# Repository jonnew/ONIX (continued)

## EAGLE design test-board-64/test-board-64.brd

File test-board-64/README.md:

# test-board-64
Test board for headstage-64. Allows injecting simulated biopotentials into
headstage modules via a selectable passive attenuator. Provides LEDs and
simulated electrical loads for optical and electrical stimulation.

## Gerber Files
{% include gerber_layers.md %}

## Bill of Materials
The BOM is located on [this google
sheet](https://docs.google.com/spreadsheets/d/1F-KWcdvH_63iXjZf0cgCfDiFX6XXW3qw6rlR8DZrFpQ/edit#gid=883728645)

## Pinout
The EIB pinout (ADC input mapping, stimulation connections, etc) is located on
[this google
sheet](https://docs.google.com/spreadsheets/d/11wRDYOqHN5lPb03yUdfXfK0zvaDYsVetplaNK-R90Gg/edit#gid=0)

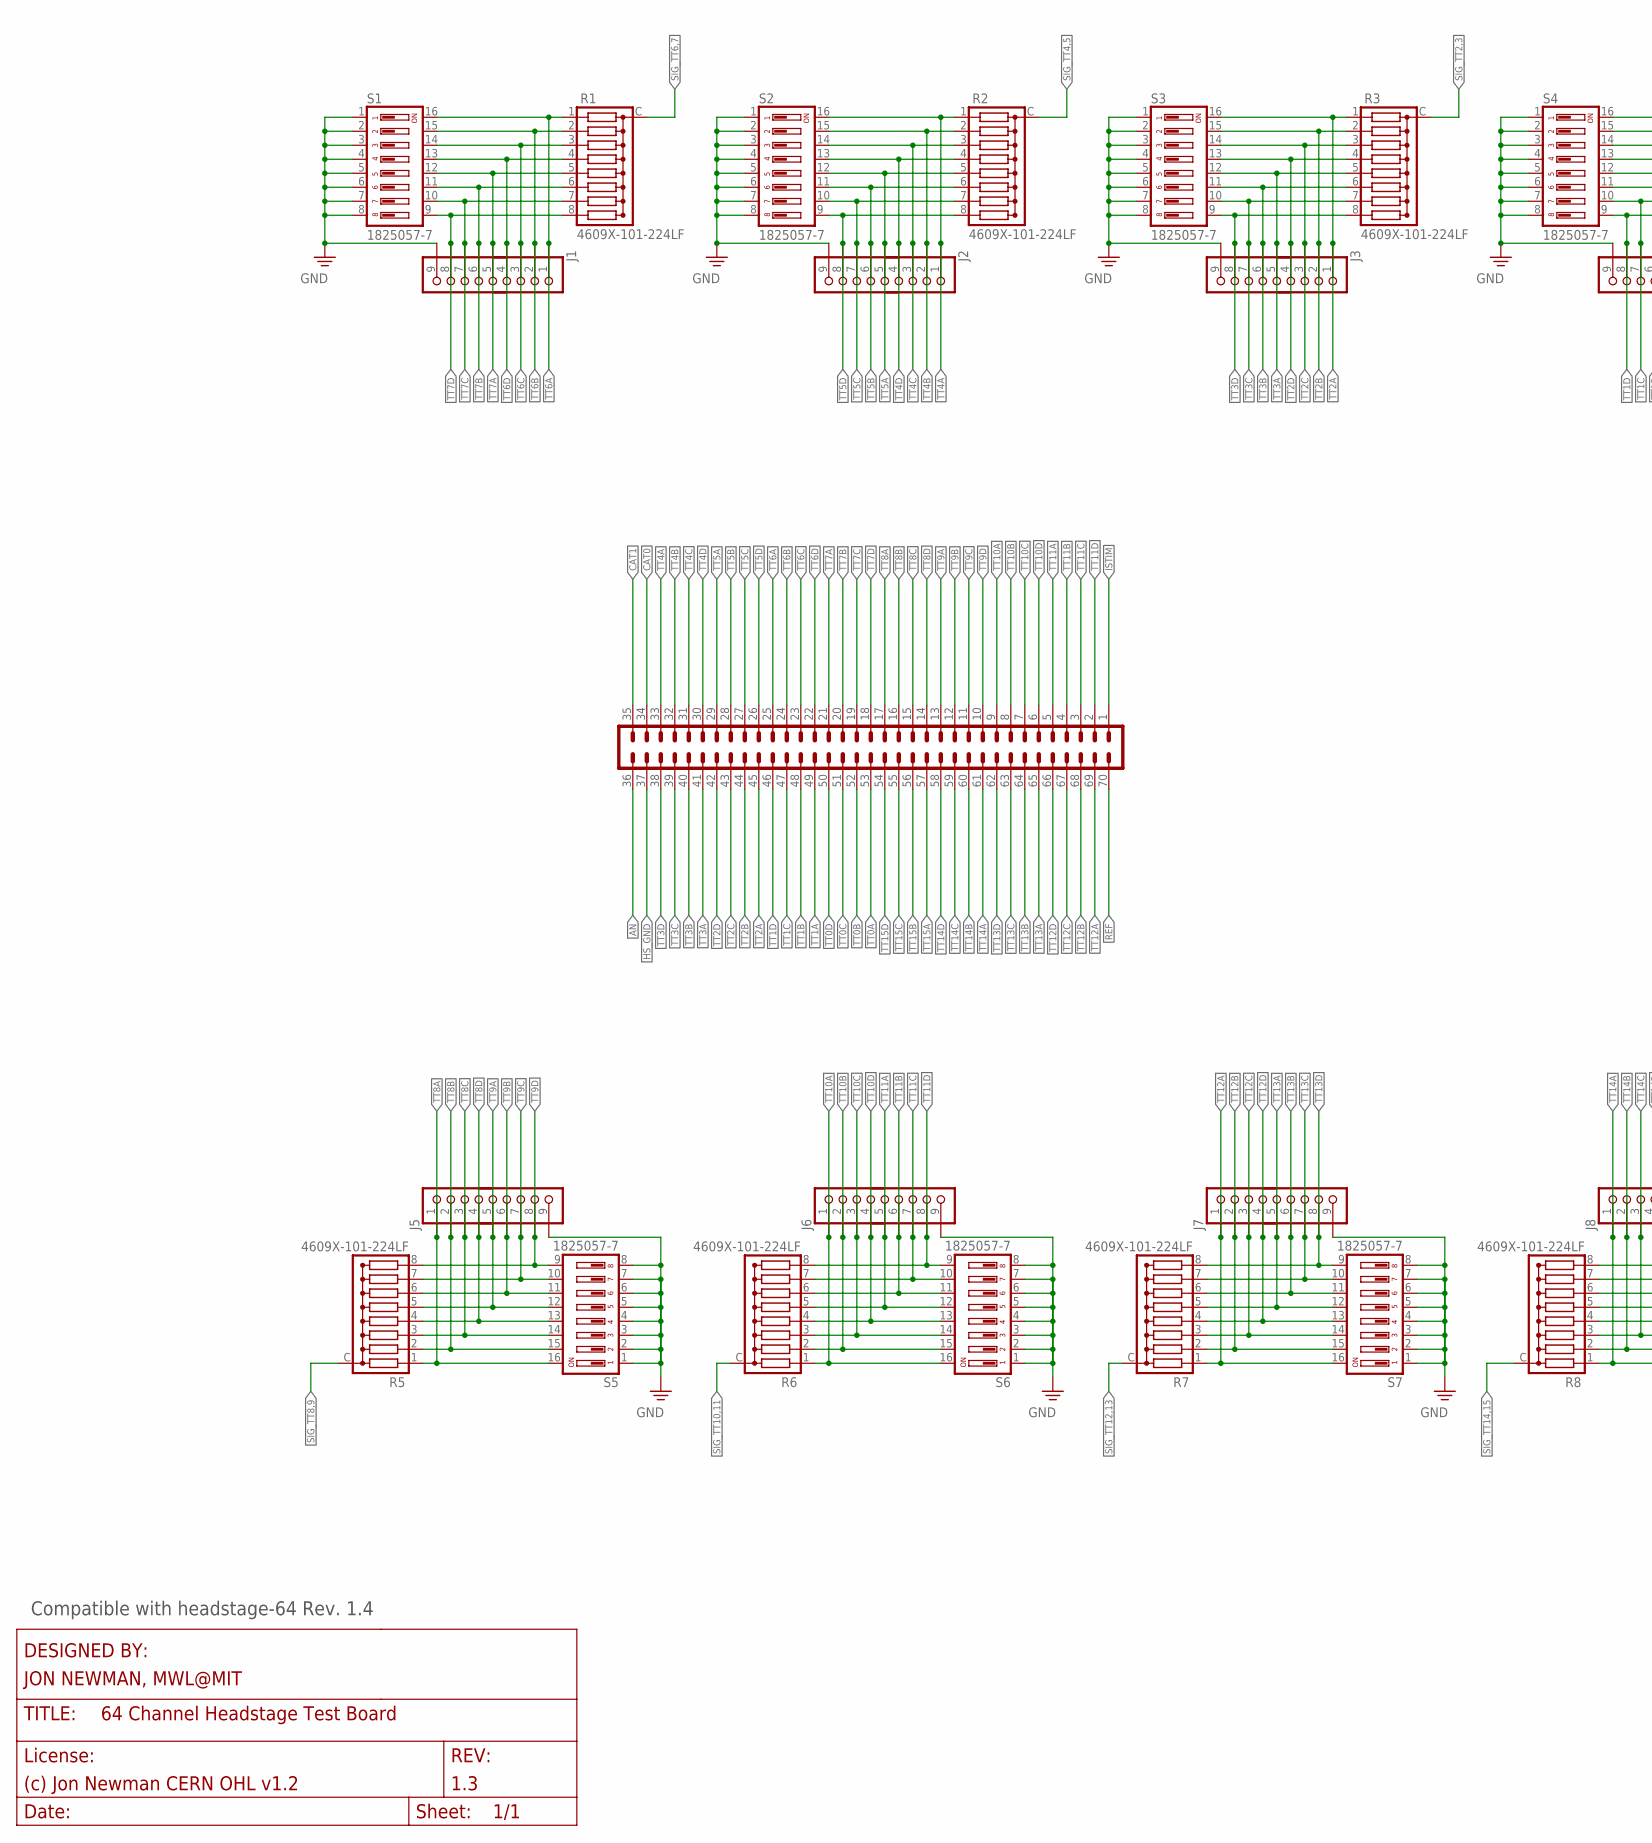
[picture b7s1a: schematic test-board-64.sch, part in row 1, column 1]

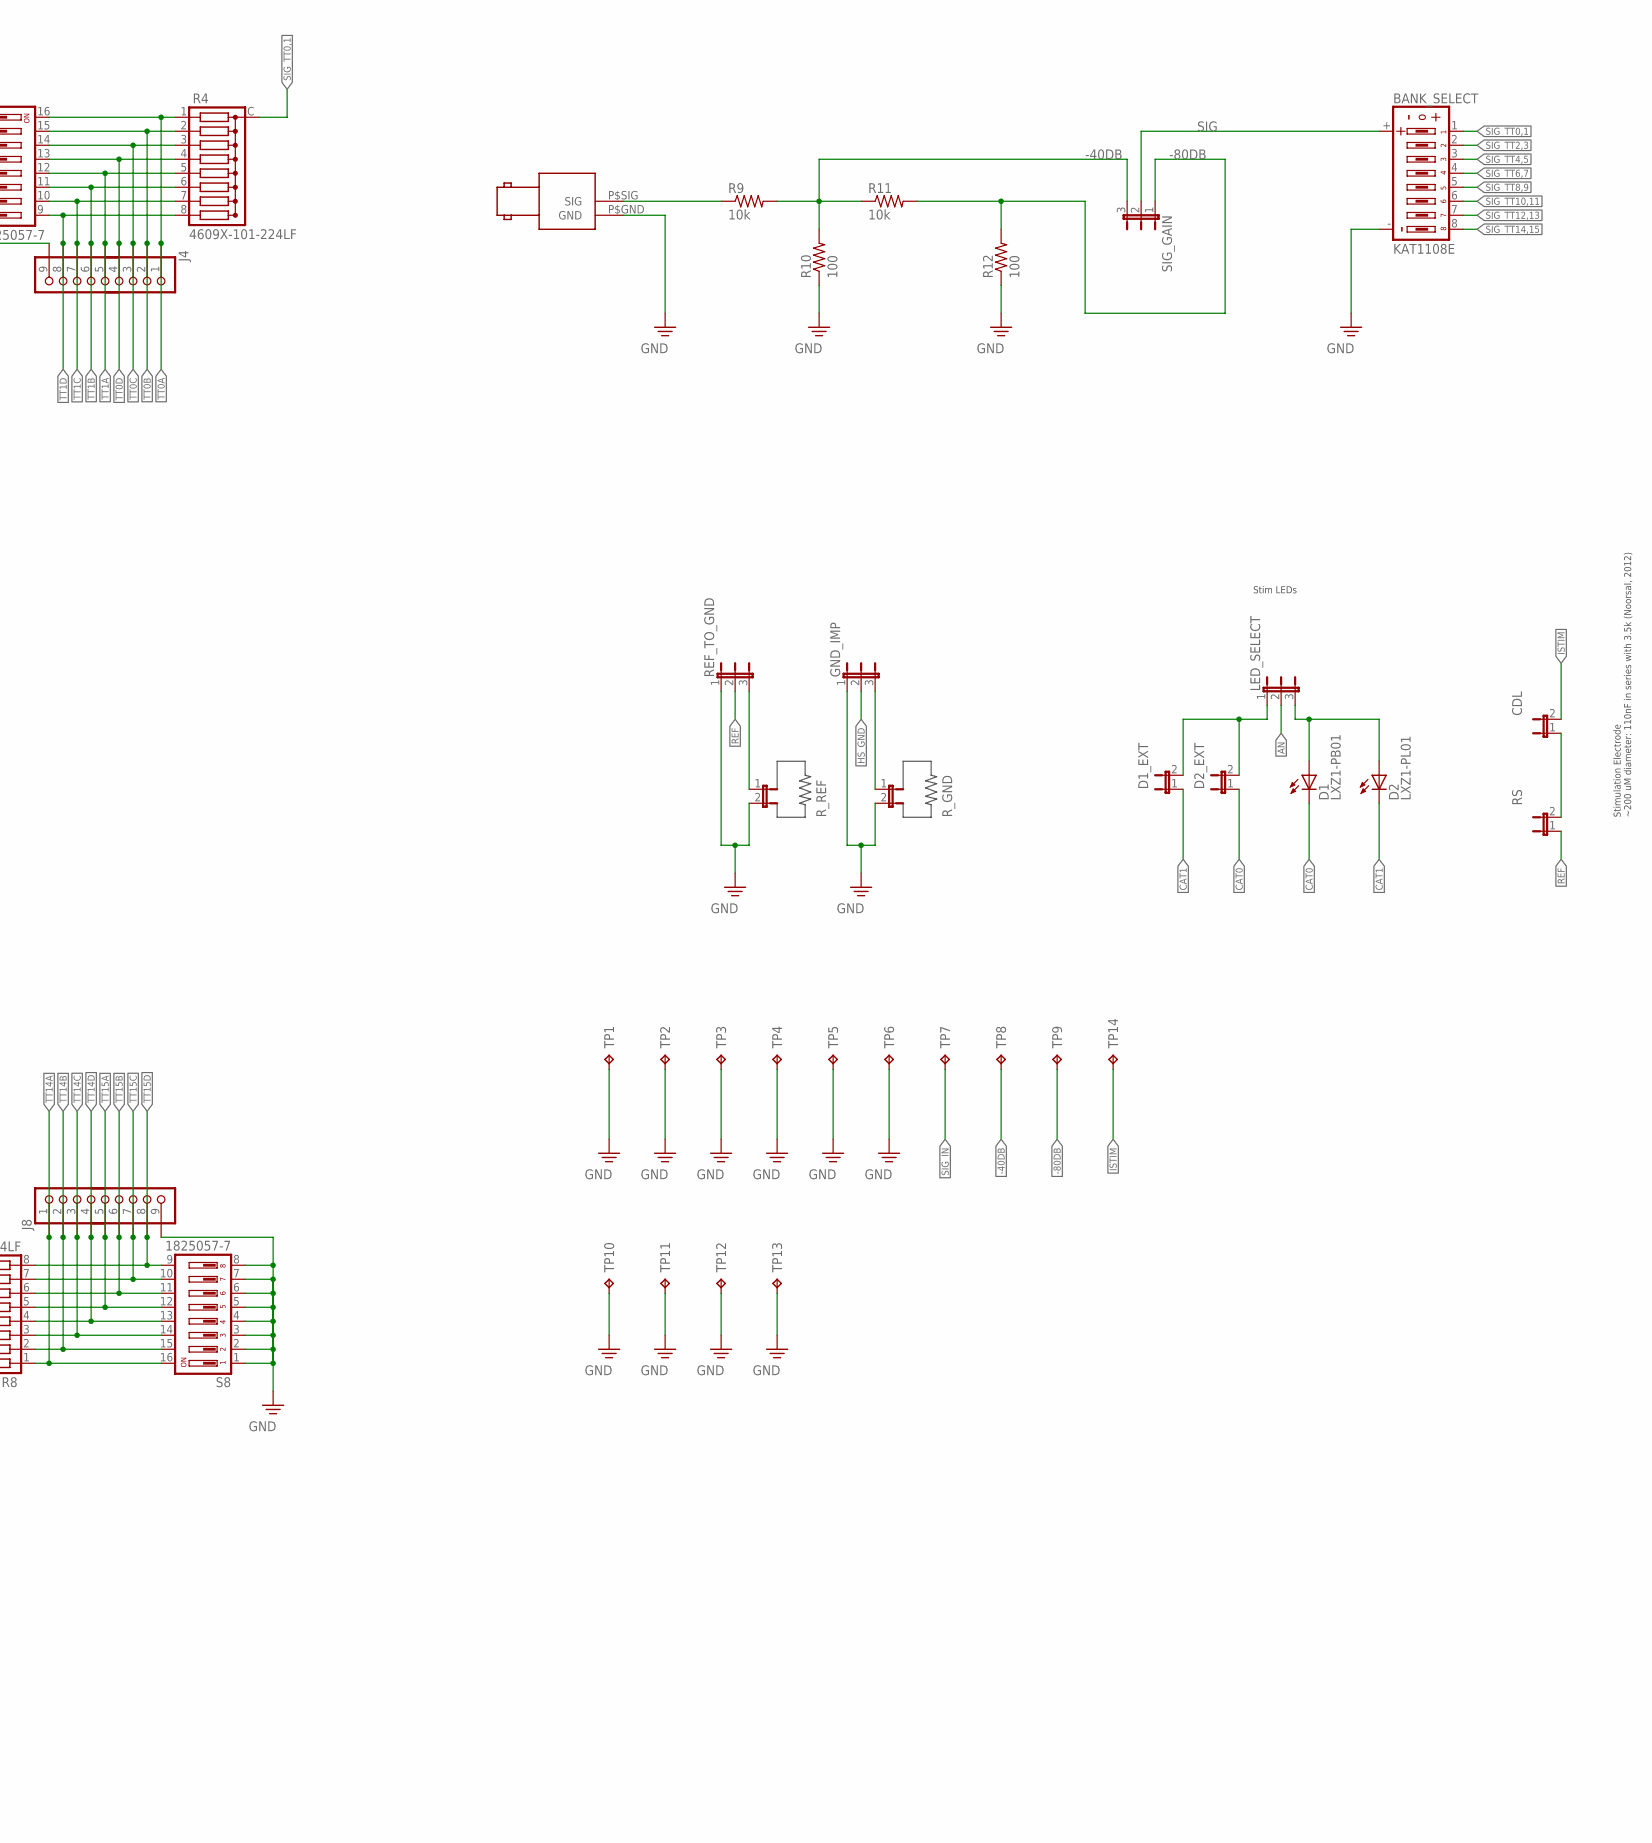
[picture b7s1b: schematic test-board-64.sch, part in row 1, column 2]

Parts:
BANK_SELECT: KAT1108E; 206-124_DIP8-SPDT
CDL: SOC2-0.1"; JP2
D1: LXZ1-PB01; LXZ1
D1_EXT, D2_EXT: SOC2-0.1"; JP2
D2: LXZ1-PL01; LXZ1
GND_IMP: JP3-0.1"; JP3
HEADSTAGE: DF40C-70DP-0.4V(51); DDF40-70REC-LRG
J1, J2, J3, J4, J5, J6, J7, J8: PINHD-1X9; 1X09
LED_SELECT: JP3-0.1"; JP3
R1, R2, R3, R4, R5, R6, R7, R8: 4609X-101-224LF; RNX8-0.1
R9, R11: 10k; 0805
R10, R12: 100; 0805
REF_TO_GND: JP3-0.1"; JP3
RS: SOC2-0.1"; JP2
R_GND: SOC2-0.1"; JP2
R_REF: SOC2-0.1"; JP2
S1, S2, S3, S4, S5, S6, S7, S8: 1825057-7; ADE_DIP8-SPST
SIG_GAIN: JP3-0.1"; JP3
SIG_IN: 1-1634622-0; BNC_RIGHT_ANGLE
TP1, TP2, TP3, TP4, TP5, TP6: GND; P1-20
TP7: SIG_IN; P1-20
TP8: -40dB; P1-20
TP9: -80dB; P1-20
TP10, TP11, TP12, TP13: TP_4-40; 4-40_PLATED
TP14: V_ESTIM; P1-20

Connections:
-40DB: R9.2, R10.2, R11.1, SIG_GAIN.3, TP8.TP
-80DB: R11.2, R12.2, SIG_GAIN.1, TP9.TP
AN: HEADSTAGE.36, LED_SELECT.2
AN_INT: D1.A, D2.A, LED_SELECT.3
CAT0: D1.C, D2_EXT.1, HEADSTAGE.34
CAT1: D1_EXT.1, D2.C, HEADSTAGE.35
GND: BANK_SELECT.-, GND_IMP.1, J1.9, J2.9, J3.9, J4.9, J5.9, J6.9, J7.9, J8.9, R10.1, R12.1, REF_TO_GND.1, R_GND.2, R_REF.2, S1.1, S1.2, S1.3, S1.4, S1.5, S1.6, S1.7, S1.8, S2.1, S2.2, S2.3, S2.4, S2.5, S2.6, S2.7, S2.8, S3.1, S3.2, S3.3, S3.4, S3.5, S3.6, S3.7, S3.8, S4.1, S4.2, S4.3, S4.4, S4.5, S4.6, S4.7, S4.8, S5.1, S5.2, S5.3, S5.4, S5.5, S5.6, S5.7, S5.8, S6.1, S6.2, S6.3, S6.4, S6.5, S6.6, S6.7, S6.8, S7.1, S7.2, S7.3, S7.4, S7.5, S7.6, S7.7, S7.8, S8.1, S8.2, S8.3, S8.4, S8.5, S8.6, S8.7, S8.8, SIG_IN.P$GND (GND), TP1.TP, TP2.TP, TP3.TP, TP4.TP, TP5.TP, TP6.TP, TP10.P$1, TP11.P$1, TP12.P$1, TP13.P$1
HS_GND: GND_IMP.2, HEADSTAGE.37
ISTIM: CDL.2, HEADSTAGE.1, TP14.TP
unnamed: D1_EXT.2, D2_EXT.2, LED_SELECT.1
unnamed: GND_IMP.3, R_GND.1
unnamed: CDL.1, RS.2
unnamed: REF_TO_GND.3, R_REF.1
REF: HEADSTAGE.70, REF_TO_GND.2, RS.1
SIG: BANK_SELECT.+, SIG_GAIN.2
SIG_IN: R9.1, SIG_IN.P$SIG (SIG), TP7.TP
SIG_TT0,1: BANK_SELECT.1, R4.C
SIG_TT2,3: BANK_SELECT.2, R3.C
SIG_TT4,5: BANK_SELECT.3, R2.C
SIG_TT6,7: BANK_SELECT.4, R1.C
SIG_TT8,9: BANK_SELECT.5, R5.C
SIG_TT10,11: BANK_SELECT.6, R6.C
SIG_TT12,13: BANK_SELECT.7, R7.C
SIG_TT14,15: BANK_SELECT.8, R8.C
TT0A: HEADSTAGE.53, J4.1, R4.1, S4.16
TT0B: HEADSTAGE.52, J4.2, R4.2, S4.15
TT0C: HEADSTAGE.51, J4.3, R4.3, S4.14
TT0D: HEADSTAGE.50, J4.4, R4.4, S4.13
TT1A: HEADSTAGE.49, J4.5, R4.5, S4.12
TT1B: HEADSTAGE.48, J4.6, R4.6, S4.11
TT1C: HEADSTAGE.47, J4.7, R4.7, S4.10
TT1D: HEADSTAGE.46, J4.8, R4.8, S4.9
TT2A: HEADSTAGE.45, J3.1, R3.1, S3.16
TT2B: HEADSTAGE.44, J3.2, R3.2, S3.15
TT2C: HEADSTAGE.43, J3.3, R3.3, S3.14
TT2D: HEADSTAGE.42, J3.4, R3.4, S3.13
TT3A: HEADSTAGE.41, J3.5, R3.5, S3.12
TT3B: HEADSTAGE.40, J3.6, R3.6, S3.11
TT3C: HEADSTAGE.39, J3.7, R3.7, S3.10
TT3D: HEADSTAGE.38, J3.8, R3.8, S3.9
TT4A: HEADSTAGE.33, J2.1, R2.1, S2.16
TT4B: HEADSTAGE.32, J2.2, R2.2, S2.15
TT4C: HEADSTAGE.31, J2.3, R2.3, S2.14
TT4D: HEADSTAGE.30, J2.4, R2.4, S2.13
TT5A: HEADSTAGE.29, J2.5, R2.5, S2.12
TT5B: HEADSTAGE.28, J2.6, R2.6, S2.11
TT5C: HEADSTAGE.27, J2.7, R2.7, S2.10
TT5D: HEADSTAGE.26, J2.8, R2.8, S2.9
TT6A: HEADSTAGE.25, J1.1, R1.1, S1.16
TT6B: HEADSTAGE.24, J1.2, R1.2, S1.15
TT6C: HEADSTAGE.23, J1.3, R1.3, S1.14
TT6D: HEADSTAGE.22, J1.4, R1.4, S1.13
TT7A: HEADSTAGE.21, J1.5, R1.5, S1.12
TT7B: HEADSTAGE.20, J1.6, R1.6, S1.11
TT7C: HEADSTAGE.19, J1.7, R1.7, S1.10
TT7D: HEADSTAGE.18, J1.8, R1.8, S1.9
TT8A: HEADSTAGE.17, J5.1, R5.1, S5.16
TT8B: HEADSTAGE.16, J5.2, R5.2, S5.15
TT8C: HEADSTAGE.15, J5.3, R5.3, S5.14
TT8D: HEADSTAGE.14, J5.4, R5.4, S5.13
TT9A: HEADSTAGE.13, J5.5, R5.5, S5.12
TT9B: HEADSTAGE.12, J5.6, R5.6, S5.11
TT9C: HEADSTAGE.11, J5.7, R5.7, S5.10
TT9D: HEADSTAGE.10, J5.8, R5.8, S5.9
TT10A: HEADSTAGE.9, J6.1, R6.1, S6.16
TT10B: HEADSTAGE.8, J6.2, R6.2, S6.15
TT10C: HEADSTAGE.7, J6.3, R6.3, S6.14
TT10D: HEADSTAGE.6, J6.4, R6.4, S6.13
TT11A: HEADSTAGE.5, J6.5, R6.5, S6.12
TT11B: HEADSTAGE.4, J6.6, R6.6, S6.11
TT11C: HEADSTAGE.3, J6.7, R6.7, S6.10
TT11D: HEADSTAGE.2, J6.8, R6.8, S6.9
TT12A: HEADSTAGE.69, J7.1, R7.1, S7.16
TT12B: HEADSTAGE.68, J7.2, R7.2, S7.15
TT12C: HEADSTAGE.67, J7.3, R7.3, S7.14
TT12D: HEADSTAGE.66, J7.4, R7.4, S7.13
TT13A: HEADSTAGE.65, J7.5, R7.5, S7.12
TT13B: HEADSTAGE.64, J7.6, R7.6, S7.11
TT13C: HEADSTAGE.63, J7.7, R7.7, S7.10
TT13D: HEADSTAGE.62, J7.8, R7.8, S7.9
TT14A: HEADSTAGE.61, J8.1, R8.1, S8.16
TT14B: HEADSTAGE.60, J8.2, R8.2, S8.15
TT14C: HEADSTAGE.59, J8.3, R8.3, S8.14
TT14D: HEADSTAGE.58, J8.4, R8.4, S8.13
TT15A: HEADSTAGE.57, J8.5, R8.5, S8.12
TT15B: HEADSTAGE.56, J8.6, R8.6, S8.11
TT15C: HEADSTAGE.55, J8.7, R8.7, S8.10
TT15D: HEADSTAGE.54, J8.8, R8.8, S8.9

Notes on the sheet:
Stimulation Electrode ~200 uM diameter: 110nF in series with 3.5k (Noorsal, 2012)
Stim LEDs
Compatible with headstage-64 Rev. 1.4

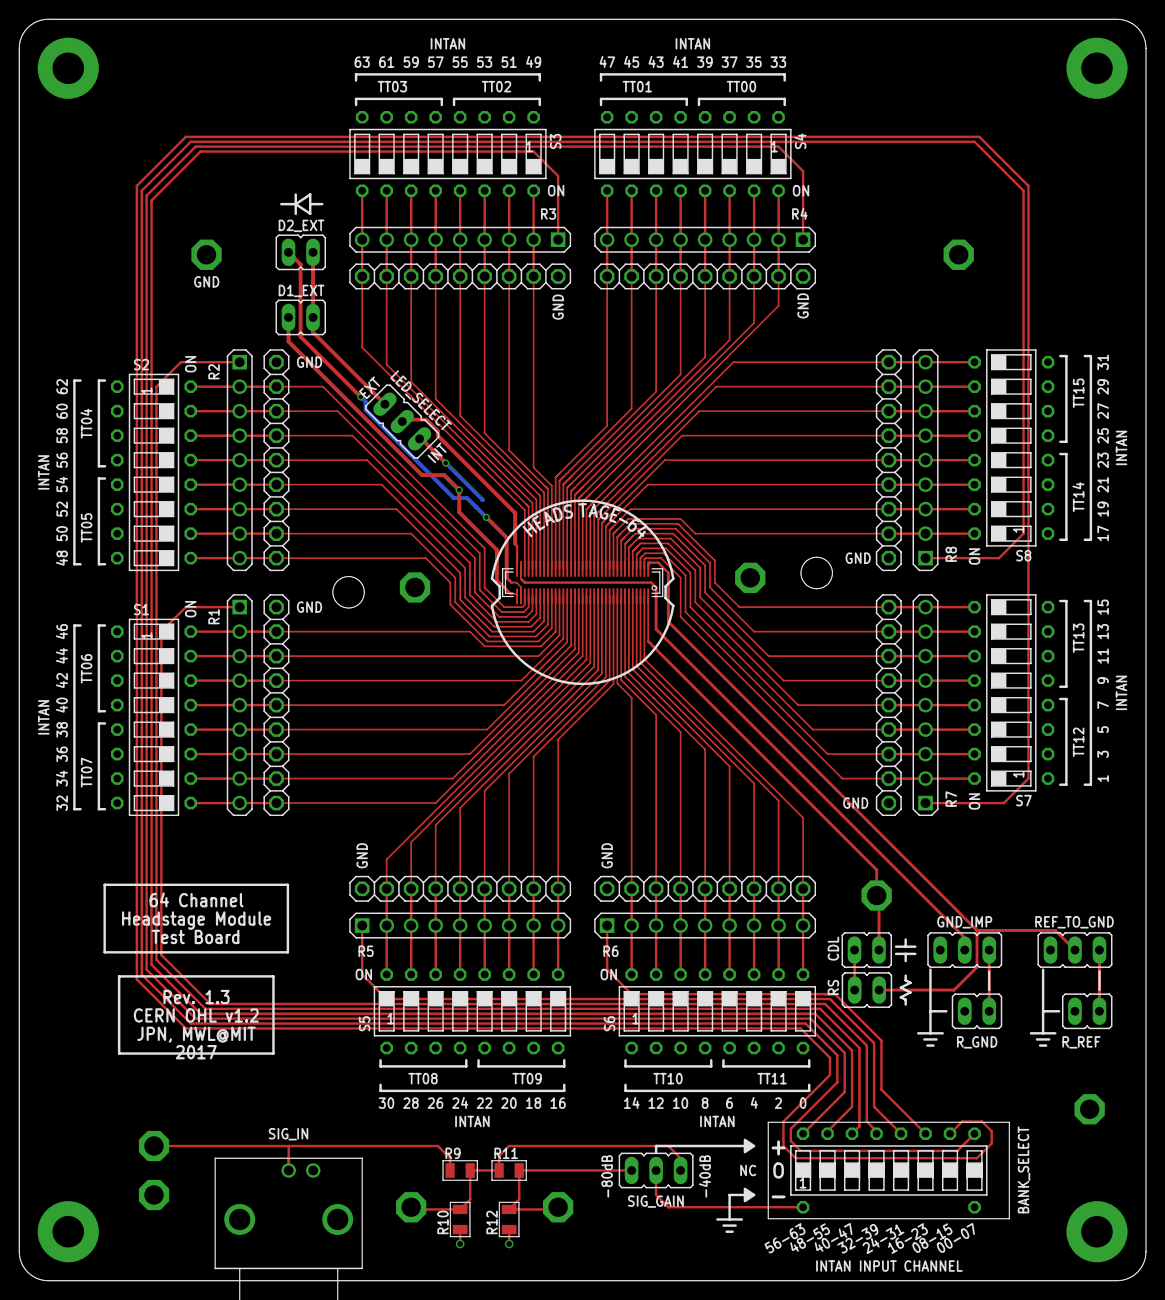
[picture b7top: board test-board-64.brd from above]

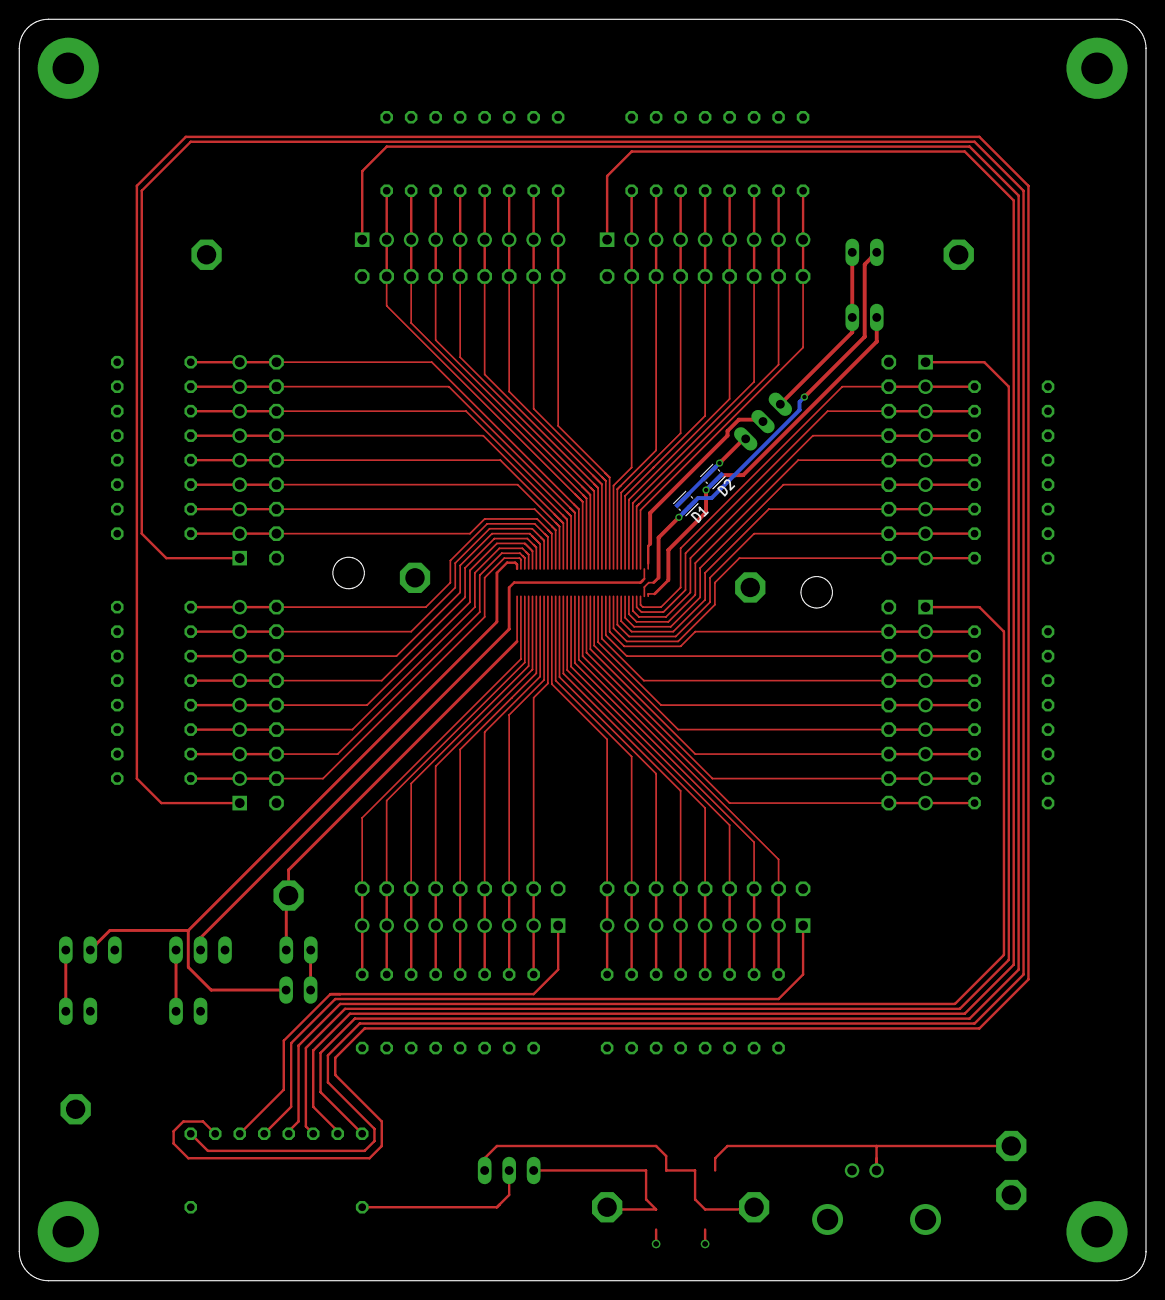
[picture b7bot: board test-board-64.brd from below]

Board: 2 copper layers, 116.8 x 130.8 mm, 57 parts (2 on the bottom side), 88 nets.

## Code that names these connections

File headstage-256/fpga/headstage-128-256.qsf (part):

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set_location_assignment PIN_P1 -to sd_irq
set_location_assignment PIN_J4 -to lh_env5
set_location_assignment PIN_J2 -to lh_data5
set_location_assignment PIN_R2 -to lh_env2
set_location_assignment PIN_P2 -to lh_data2
set_location_assignment PIN_C14 -to lH_data1
set_location_assignment PIN_C15 -to lh_env1
set_location_assignment PIN_D12 -to led_sin
set_location_assignment PIN_E11 -to led_clk
set_location_assignment PIN_E14 -to led_latch
set_location_assignment PIN_E15 -to potb_cs
set_location_assignment PIN_F11 -to lh_data6
set_location_assignment PIN_F12 -to lh_env6
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set_location_assignment PIN_H13 -to sclk
set_location_assignment PIN_L11 -to sda
set_location_assignment PIN_K11 -to scl
set_location_assignment PIN_M14 -to status_a
set_location_assignment PIN_L15 -to status_b
set_location_assignment PIN_J5 -to stim_null_a
set_location_assignment PIN_H3 -to pota_cs
set_location_assignment PIN_G2 -to dac_a_cs
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set_location_assignment PIN_F5 -to exp3
set_location_assignment PIN_G5 -to exp4
set_location_assignment PIN_R5 -to imu_int
set_location_assignment PIN_P4 -to imu_reset
set_location_assignment PIN_R7 -to exp9
set_location_assignment PIN_P8 -to exp10
set_location_assignment PIN_N8 -to exp13
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set_location_assignment PIN_B6 -to serdes_gpio0
set_location_assignment PIN_B7 -to serdes_gpio2
set_location_assignment PIN_A7 -to serdes_gpio3
set_location_assignment PIN_D7 -to din0
set_location_assignment PIN_B8 -to din1
set_location_assignment PIN_C8 -to din2
set_location_assignment PIN_A9 -to din3
set_location_assignment PIN_E7 -to din4
set_location_assignment PIN_E9 -to din5
set_location_assignment PIN_D10 -to din6
set_location_assignment PIN_E10 -to din7
set_location_assignment PIN_A11 -to din8
set_location_assignment PIN_B11 -to din9
set_location_assignment PIN_B12 -to din10
set_location_assignment PIN_D11 -to din11
set_location_assignment PIN_B14 -to serdes_scl
set_location_assignment PIN_A14 -to pclk
set_location_assignment PIN_B15 -to serdes_sda
set_location_assignment PIN_B13 -to vsync
set_location_assignment PIN_A13 -to hsync
set_global_assignment -name PARTITION_NETLIST_TYPE SOURCE -section_id Top
set_global_assignment -name PARTITION_FITTER_PRESERVATION_LEVEL PLACEMENT_AND_ROUTING -section_id Top
set_global_assignment -name PARTITION_COLOR 16764057 -section_id Top
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
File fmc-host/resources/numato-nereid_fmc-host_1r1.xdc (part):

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set_property -dict { PACKAGE_PIN "AE25"   IOSTANDARD LVCMOS33       SLEW FAST} [get_ports { LA04_N              }]   ;          # IO_L23N_T3_12                 Sch = LA04_N            FMC = H11
set_property -dict { PACKAGE_PIN "W25"    IOSTANDARD LVCMOS33       SLEW FAST} [get_ports { AIN/OUT9            }]   ;          # IO_L5P_T0_12                  Sch = LA05_P            FMC = D11
set_property -dict { PACKAGE_PIN "W26"    IOSTANDARD LVCMOS33       SLEW FAST} [get_ports { LA05_N              }]   ;          # IO_L5N_T0_12                  Sch = LA05_N            FMC = D12
set_property -dict { PACKAGE_PIN "Y25"    IOSTANDARD LVCMOS33       SLEW FAST} [get_ports { DEBUG0              }]   ;          # IO_L10P_T1_12                 Sch = LA06_P            FMC = C10
set_property -dict { PACKAGE_PIN "Y26"    IOSTANDARD LVCMOS33       SLEW FAST} [get_ports { DEBUG1              }]   ;          # IO_L10N_T1_12                 Sch = LA06_N            FMC = C11
set_property -dict { PACKAGE_PIN "V23"    IOSTANDARD LVCMOS33       SLEW FAST} [get_ports { ADC_CONVST          }]   ;          # IO_L3P_T0_DQS_12              Sch = LA07_P            FMC = H13
set_property -dict { PACKAGE_PIN "V24"    IOSTANDARD LVCMOS33       SLEW FAST} [get_ports { DAC_MOSI            }]   ;          # IO_L3N_T0_DQS_12              Sch = LA07_N            FMC = H14
set_property -dict { PACKAGE_PIN "U26"    IOSTANDARD LVCMOS33       SLEW FAST} [get_ports { LA08_P              }]   ;          # IO_L4P_T0_12                  Sch = LA08_P            FMC = G12
set_property -dict { PACKAGE_PIN "V26"    IOSTANDARD LVCMOS33       SLEW FAST} [get_ports { LA08_N              }]   ;          # IO_L4N_T0_12                  Sch = LA08_N            FMC = G13
set_property -dict { PACKAGE_PIN "W20"    IOSTANDARD LVCMOS33       SLEW FAST} [get_ports { DEBUG2              }]   ;          # IO_L15P_T2_DQS_12             Sch = LA09_P            FMC = D14
set_property -dict { PACKAGE_PIN "Y21"    IOSTANDARD LVCMOS33       SLEW FAST} [get_ports { DEBUG4              }]   ;          # IO_L15N_T2_DQS_12             Sch = LA09_N            FMC = D15
set_property -dict { PACKAGE_PIN "V21"    IOSTANDARD LVCMOS33       SLEW FAST} [get_ports { DEBUG3              }]   ;          # IO_L6P_T0_12                  Sch = LA10_P            FMC = C14
set_property -dict { PACKAGE_PIN "W21"    IOSTANDARD LVCMOS33       SLEW FAST} [get_ports { DEBUG5              }]   ;          # IO_L6N_T0_VREF_12             Sch = LA10_N            FMC = C15
set_property -dict { PACKAGE_PIN "L19"    IOSTANDARD LVCMOS33       SLEW FAST} [get_ports { LA11_P              }]   ;          # IO_L21P_T3_DQS_15             Sch = LA11_P            FMC = H16
set_property -dict { PACKAGE_PIN "L20"    IOSTANDARD LVCMOS33       SLEW FAST} [get_ports { LA11_N              }]   ;          # IO_L21N_T3_DQS_A18_15         Sch = LA11_N            FMC = H17
set_property -dict { PACKAGE_PIN "M17"    IOSTANDARD LVCMOS33       SLEW FAST} [get_ports { LA12_P              }]   ;          # IO_L23P_T3_FOE_B_15           Sch = LA12_P            FMC = G15
set_property -dict { PACKAGE_PIN "L18"    IOSTANDARD LVCMOS33       SLEW FAST} [get_ports { LA12_N              }]   ;          # IO_L23N_T3_FWE_B_15           Sch = LA12_N            FMC = G16
set_property -dict { PACKAGE_PIN "K20"    IOSTANDARD LVCMOS33       SLEW FAST} [get_ports { LA13_P              }]   ;          # IO_L19P_T3_A22_15             Sch = LA13_P            FMC = D17
set_property -dict { PACKAGE_PIN "J20"    IOSTANDARD LVCMOS33       SLEW FAST} [get_ports { LA13_N              }]   ;          # IO_L19N_T3_A21_VREF_15        Sch = LA13_N            FMC = D18
set_property -dict { PACKAGE_PIN "J18"    IOSTANDARD LVCMOS33       SLEW FAST} [get_ports { DEBUG6              }]   ;          # IO_L20P_T3_A20_15             Sch = LA14_P            FMC = C18
set_property -dict { PACKAGE_PIN "J19"    IOSTANDARD LVCMOS33       SLEW FAST} [get_ports { DEBUG7              }]   ;          # IO_L20N_T3_A19_15             Sch = LA14_N            FMC = C19
set_property -dict { PACKAGE_PIN "U17"    IOSTANDARD LVCMOS33       SLEW FAST} [get_ports { AIN/OUT0            }]   ;          # IO_L23P_T3_13                 Sch = LA15_P            FMC = H19
set_property -dict { PACKAGE_PIN "T17"    IOSTANDARD LVCMOS33       SLEW FAST} [get_ports { LA15_N              }]   ;          # IO_L23N_T3_13                 Sch = LA15_N            FMC = H20
set_property -dict { PACKAGE_PIN "T18"    IOSTANDARD LVCMOS33       SLEW FAST} [get_ports { AIN/OUT2            }]   ;          # IO_L19P_T3_13                 Sch = LA16_P            FMC = G18
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set_property -dict { PACKAGE_PIN "H18"    IOSTANDARD LVCMOS33       SLEW FAST} [get_ports { LA30_N              }]   ;          # IO_L14N_T2_SRCC_15            Sch = LA30_N            FMC = H35
set_property -dict { PACKAGE_PIN "G19"    IOSTANDARD LVCMOS33       SLEW FAST} [get_ports { DES_PDN_B           }]   ;          # IO_L16P_T2_A28_15             Sch = LA31_P            FMC = G33
set_property -dict { PACKAGE_PIN "F20"    IOSTANDARD LVCMOS33       SLEW FAST} [get_ports { LA31_N              }]   ;          # IO_L16N_T2_A27_15             Sch = LA31_N            FMC = G34
set_property -dict { PACKAGE_PIN "H19"    IOSTANDARD LVCMOS33       SLEW FAST} [get_ports { LINK_A_PWR_EN       }]   ;          # IO_L18P_T2_A24_15             Sch = LA32_P            FMC = H37
set_property -dict { PACKAGE_PIN "G20"    IOSTANDARD LVCMOS33       SLEW FAST} [get_ports { LINK_PWR_ADJ_SCLK   }]   ;          # IO_L18N_T2_A23_15             Sch = LA32_N            FMC = H38
set_property -dict { PACKAGE_PIN "L17"    IOSTANDARD LVCMOS33       SLEW FAST} [get_ports { LA33_P              }]   ;          # IO_L24P_T3_RS1_15             Sch = LA33_P            FMC = G36
set_property -dict { PACKAGE_PIN "K18"    IOSTANDARD LVCMOS33       SLEW FAST} [get_ports { LA33_N              }]   ;          # IO_L24N_T3_RS0_15             Sch = LA33_N            FMC = G37
set_property -dict { PACKAGE_PIN "P23"    IOSTANDARD LVCMOS33       SLEW FAST} [get_ports { MLVDS_DI_1          }]   ;          # IO_L11P_T1_SRCC_13            Sch = HA00_CC_P         FMC = F4
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set_property -dict { PACKAGE_PIN "M20"    IOSTANDARD LVCMOS33       SLEW FAST} [get_ports { HA04_N              }]   ;          # IO_L7N_T1_13                  Sch = HA04_N            FMC = F8
set_property -dict { PACKAGE_PIN "R18"    IOSTANDARD LVCMOS33       SLEW FAST} [get_ports { HA05_P              }]   ;          # IO_L24P_T3_13                 Sch = HA05_P            FMC = E6
set_property -dict { PACKAGE_PIN "P18"    IOSTANDARD LVCMOS33       SLEW FAST} [get_ports { HA05_N              }]   ;          # IO_L24N_T3_13                 Sch = HA05_N            FMC = E7
set_property -dict { PACKAGE_PIN "P16"    IOSTANDARD LVCMOS33       SLEW FAST} [get_ports { ADC_MOSI            }]   ;          # IO_L20P_T3_13                 Sch = HA06_P            FMC = K10
set_property -dict { PACKAGE_PIN "N17"    IOSTANDARD LVCMOS33       SLEW FAST} [get_ports { ADC_MISO_A          }]   ;          # IO_L20N_T3_13                 Sch = HA06_N            FMC = K11
set_property -dict { PACKAGE_PIN "R16"    IOSTANDARD LVCMOS33       SLEW FAST} [get_ports { AIN/OUT5            }]   ;          # IO_L21P_T3_DQS_13             Sch = HA07_P            FMC = J9
set_property -dict { PACKAGE_PIN "R17"    IOSTANDARD LVCMOS33       SLEW FAST} [get_ports { ADC_MISO_B          }]   ;          # IO_L21N_T3_DQS_13             Sch = HA07_N            FMC = J10
set_property -dict { PACKAGE_PIN "U19"    IOSTANDARD LVCMOS33       SLEW FAST} [get_ports { nADC_RESET          }]   ;          # IO_L18P_T2_13                 Sch = HA08_P            FMC = F10
set_property -dict { PACKAGE_PIN "U20"    IOSTANDARD LVCMOS33       SLEW FAST} [get_ports { AIN/OUT8            }]   ;          # IO_L18N_T2_13                 Sch = HA08_N            FMC = F11
set_property -dict { PACKAGE_PIN "N18"    IOSTANDARD LVCMOS33       SLEW FAST} [get_ports { HA09_P              }]   ;          # IO_L22P_T3_13                 Sch = HA09_P            FMC = E9
set_property -dict { PACKAGE_PIN "M19"    IOSTANDARD LVCMOS33       SLEW FAST} [get_ports { HA09_N              }]   ;          # IO_L22N_T3_13                 Sch = HA09_N            FMC = E10
set_property -dict { PACKAGE_PIN "T20"    IOSTANDARD LVCMOS33       SLEW FAST} [get_ports { nADC_CS             }]   ;          # IO_L16P_T2_13                 Sch = HA10_P            FMC = K13
set_property -dict { PACKAGE_PIN "R20"    IOSTANDARD LVCMOS33       SLEW FAST} [get_ports { HA10_N              }]   ;          # IO_L16N_T2_13                 Sch = HA10_N            FMC = K14
set_property -dict { PACKAGE_PIN "P19"    IOSTANDARD LVCMOS33       SLEW FAST} [get_ports { ADC_BUSY            }]   ;          # IO_L9P_T1_DQS_13              Sch = HA11_P            FMC = J12
set_property -dict { PACKAGE_PIN "P20"    IOSTANDARD LVCMOS33       SLEW FAST} [get_ports { ADC_SCLK            }]   ;          # IO_L9N_T1_DQS_13              Sch = HA11_N            FMC = J13
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
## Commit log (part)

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2018-04-24 Reorganized and revised system specification
    - Up to date
    - Logical devision of content
    - Updated API documentation
2018-05-18 Replaced stim null circuit on both headstages
    - ADG140x was replaced with dg509b, which is a 2 circuit 1-to-4 mux.
    This allows the electrode path to be completely disconnected from
    stimulation circuitry during idle periods. During idle periods,
    stimuluation output is shunted to ground through a dummy load so that
    offsets to not develop large voltages during idle periods.
    - Additionally, the inverting node of the estim current source amplifier
2018-07-09 headstage-256 rev 1.1
    - Should be ready for speedy
    - 8 layer board should fix radio-freq isolation issue on previous
    version
    - Other small circuit modifications and fixes
2018-07-18 pcie-host board rev. 1.2
    - Extra bidirectional isolator added to propogate LOCK and PASS signals from deserializer to host FPGA.
    - Immediate non-isolated and isolated SMA IO added.
    - Routed HSYNC to normal (LA) differential pins rather than dedicated
    clock input which was causing synthesis issues.
2018-07-20 Improvements to clroepcie
    - Overloads for get_opt directly in clr binding. Should do this for
    set_opt as well and get rid of DispoIntPtr entirely.
2018-07-23 Bring Intan AUX inputs to eib-256 from headstage-256
    - There were several unused pins on eib-256.
    - I brought two of the Intan AUX inputs from amplifiers A and B and one
    from C and D to these unused pins. Test point connections on the
    headstage were preserved.
    - eib-128 will not be modified because these pins use the amp C
    and D headers. A and B headers are occupied with e/o-stim connections.
2018-07-25 Produced gerbers for headstage-256 rev. 1.1
    - Should be ready for production
    - Updated schematic
2018-07-30 Added sizing sketch for mezzanine board on headstage-64
2018-08-10 Many fixes to new 8-layer routing
    - Replace ultra thin power traces
    - Proper z on differential pairs
    - Decoupling elements moved to corresponding ICs
    - Remove thin gnd wiring and use planes
2018-08-17 Updated headstage-256 revision to 1.1.
2018-08-22 Update deprated serdes-interface to most current version
    - FPGA moved to top
    - Estim circuit
2018-08-27 eib-64 rev. 1.1
    - Fits latest shuttle drive reatining feature.
2018-10-07 headstage-256 rev 1.1 and headstage-64 rev. 1.2
    - These should be ready for fabrication
    - Extensive DRU and manual checking on both designs
    - Howland current source integrated into both designs
    - MPU9250 replace with ICM-20948 on headstage-64 since MPU is deprecated
    - Gerbers update and gerbv project files as well
    - Schematics of both headstages updated
2018-10-14 Github site update
    - Bring READMEs up to date, more or less
    - Files for local Jekyll build
    - All pdfs, images, etc moved to LFS
2018-10-27 Make liboepcie thread safe
    - Be careful -- performance hit in some cases because we are funneling
    through syscalls
2018-11-01 Update xillybus backend instructions
    - Included high bw write stream
    - Fix broken image link
2018-12-05 Fixed mising vcoax trace on bno55 variant
2018-12-23 WIP of version 2.1.0 of oepcie API
    - oe_write_frame() prototype replaced with oe_write(), which can write
    block data to particular devices.
    - Block read size is now a context option
    - CLR and C++ bindings implement c library changes and appear to work.
    - More extensive testing is required
    - API docs and spec need to be updated
2019-01-02 Minor changes to headstage-64 while updating BOM
    - stencil size reduced for dfn diode packages to prevent shorting
2019-01-20 FMC host module
    - This will deprecate pcie-host
    - Should conform, largely, to VITA-57 standardFeatures
    - 1 deserializer
    - 2 arbitrary logic-level rugged GPIs
    - 1 arbitrary logic-level rugged GPO
    - 8 16-bit analog outputs
2019-01-23 Moved vias in io breakout away from screws
2019-01-23 Update gerbers for analog-io-breakout board
2019-01-24 Connected screw terminal rows in analog io board
2019-02-10 Minor changes to liboepcie during debugging
    - Added test device
2019-02-25 updated breakout board shell
2019-03-02 Fixed BNC footprint in analog-io-breakout -also added grounded mounting hole and fixed label spacing
2019-03-05 Updates to fmc-breakout after talking with Jakob
    - Moved origin to upper left corner
    - Increased hole sizes on BNC connectors
    - Moved high speed section to top of board s.t. it is next to the other
    input connector
2019-03-06 Increased size of BNC through holes on breakout board
    - As per jakob's request
2019-04-29 Some minor api modifications and fixes
    - Remove unessesary resets from acquisition startup since this is handled
    in oe_init_ctx
2019-06-03 Fix syntax error in oelogo.h
    - Dangling string after ;
2019-07-28 Lighthouse-booster Rev. 1.1
    - Minor fixes to version 1.0 after testing
    - Replaced 0 ohm jumpers between gate driver and gate with 47 kOhm
    pulldowns to prevent possible DC damage to LEDs when board is not
    driven
    - Decrease current limit resistors to 360 mOhm. This should give us 5
    Amps per LED string after empirical testing
2019-07-29 Added Speedy order number to fabrication file README
2019-08-09 Added LMK61E2
    Should solve the issue of how to make 93.6 MHz, but is pretty huge
2019-08-12 fmc-host rev. 1.1
    - Completed revision 1.1 of the FMC host module
    - Needs final synthesis testing before fab
2019-08-16 Breakout board WIP
    - added shiftreg to read keys and relay status
    - added power supply
    - added relays
    - added lvds/se converters
2019-08-19 Fixed flat-flex connector part number on headstage-neuropix
    - Also, updated PDF of schematic
2019-08-22 Added encoder datasheet
2019-08-26 Breakout board layout and circuit fixes
    - Many fixes to schematic ERC and board layout
    - Added serial to parallel digital IO
2019-08-29 Update headstage-64 and headstage-256 schematics
    - I did this while double checking the BOM for Filipe
    - Divide functional blocks into labeled sections
    - Add images of schematics to the READMEs
2019-09-01 breakout case WIP
2019-09-22 Add smd centroids to headstage-64
2019-09-27 Lighthouse booster rev. 1.2
    - Added a monostable vibrator to the high-side power-switch trigger
    circuit in order to prevent the system 12V from seeing any of the LED
    circuit when the LEDs are active.
    - This circuit re-triggers on every incoming sync pulse so that a
    perfect envelope is formed to disconnected the system 12V from the LED
    12V whenever a sync train is being applied
2019-10-02 added first draft of 128 EIB with omnetics connectors
2019-10-07 Added some very rudimentary firmware for the breakout board
    - Display a main menu on the OLED using littlevgl
    - Control it with a rotary encoder
    - littlevgl config file is included and needs to be copied to the base
    directory of the littlevgl library before using this
2019-10-30 Update API with neuropixels 1.0 device definitions
2019-11-17 Updates to fmc-host board when testing revision 1.3
    - This is starting revision 1.4
    - Replaced SPDT analog switches for analog IO with SPST swiches inline
    with the analog outpus. Inputs are always connected. This allows
    loopback of analog output instead of wasting the analog input
    capabilites when a line is selected to be an output
2019-11-22 Fix wrong paths in test app
2019-11-25 Update EIBs and add eib-64-large
    - eib-64-large is identical to eib-64, except that it fits large shuttle
    drives. It is intended as stand in for early adopters who work with rats
    and want to use the large shuttle drive
    - Update READMEs of other EIBs
2019-11-27 Add driver makefile and adapt main one
2019-12-07 headstage-neuropix rev 1.2
    - Dual neuropixels probe support
    - 2X HTC Vive receivers
    - Many changes made for reliability of manufacturing
2019-12-18 Updated C++ bindings to work with driver functionality
    - The context_t constructor now takes driver context option arguments
    that are needed before initialization using a variadic constructor.
    Option value pairs are provided using a driver_arg_t = std::pair<int, T>.
    - I also fixed some issues with the code when setting options that are
    pointer types to begin with, instead of non pointers. To do this, I made
    use of the C++17's if constexpr functionality
2020-01-07 Basic sizing for updated breakout board case
    - Needs fit check
    - Needs draft angles
    - Needs to be split in 2 parts
    - Add cutouts for laser cut top panels?
2020-02-06 headstage-64 rev. 1.4 along with all dependencies
    - This is headstage-64 revision 1.4. Because it involves a change in the
    bottom analog connector, a lot of other boards had to be changed to
    match the new pinout. That is why there are so many files in this
    commit. Changes in revision 1.4 and affects on other boards are as
    follows:
    1. The coaxial adapter board has been improved to allow a regulator to
2020-02-09 Remove erroneos LED values from silk layer of fmc-host
2020-03-09 Final headstage-neuropix rev. 1.2
    - BOM simplification while updating the google sheet
    - Small PCB changes
2020-04-15 Lock the handle when initializing riffa
2020-04-20 Add riffa lib VS project files
2020-05-07 Initial commit drive&headstage size & weight comparison
2020-06-02 More updates to headstage-neuropix after review from Speedy
    - Many bottom side pads moved apart to allow solder mask in between and
    to prevent shorts
2020-06-08 Added headstage-64/revisions/rev-1.3
    - Contains board designs, fab files, BOM, etc for headstage-64 rev 1.3,
    which is used in several labs and distributed with the beta-test kit
2020-06-08 Added frozen eib-64-large/revisions/rev-1.0
    - This is the beta-test version of eib-64-large
2020-06-09 Add SHA for test-board-64/revisions/rev-1.2
2020-07-02 clroni version 3.1.1
    - Replaced device map naming with device table
    - contex.DeviceTable is now a Dictionary rather than a List
    - Update nuget package
2020-07-13 Got rid of accidentally added temporary files
2020-08-03 Deprecate lighthouse-booster
    - We are moving the V2 of the lighthouse system which solves the range
    issue that the booster was meant to address
2020-08-10 Remove defunt .gitmodules
2020-09-01 Breakout case WIP
    non functional, needs to be updated to newer pcb
2020-09-04 Added waterejet DXF files for case to get quotes ready
2020-10-09 Increased space between IDC headers and wire terminals on breakout
    - Moved by 2mm so that an IDC connector can actually plug into the
    header.
2021-02-11 Added more room for caps in breakout case
    Changed circular cutouts on bottom side of the case facing the PCB to longer slots to make more room for components. Should fix issue that filipe just encountered on first test assembly for beta-test.
2021-03-16 Update breakout firmware README.md
    - Get rid of PLL info since its clearly visible in the code
2021-04-06 Fully functional breakout firmware
    - Integrated preprocessor switches into the code so that changes do not
    need to be made to run simulations
    - Digital input sampling now occurs on falling edge of LVDS_OUT[0] which
    put it 180 deg. out of phase with when its latched to prevent
    metastability
    - Other very small changes
2021-05-26 Add IRFML8244 N-MOSFET datasheet to breakout/datasheets
2021-05-30 Add archive notice to headstage-neuropix/README
    - Development has been moved to https://github.com/open-ephys/onix-headstage-neuropix1
